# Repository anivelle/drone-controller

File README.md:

# PID Drone Controller

This is my repository for the drone controller I am building using the Arduino
Nano 33 BLE. This is an exercise for me in working directly with the Arduino's
hardware peripherals, as well as learning about PID (I have never taken a
feedback control course).

I'll be using some sort of time of flight (TOF) sensor to give the drone the
ability to hover at a certain height, along with a 9-axis IMU (currently the
BNO055 because I have it) to keep the drone stabilized in the air. That is all
that is currently planned, but if I enjoy this enough I might try autonomous
movement.

ICM-20948 code pulled from [Sparkfun's Arduino
Library](https://github.com/sparkfun/SparkFun_ICM-20948_ArduinoLibrary/tree/main)
because it turns out the DMP-related code is far more complex than I need to
work with. I am trying to reinvent the wheel, but not that much.

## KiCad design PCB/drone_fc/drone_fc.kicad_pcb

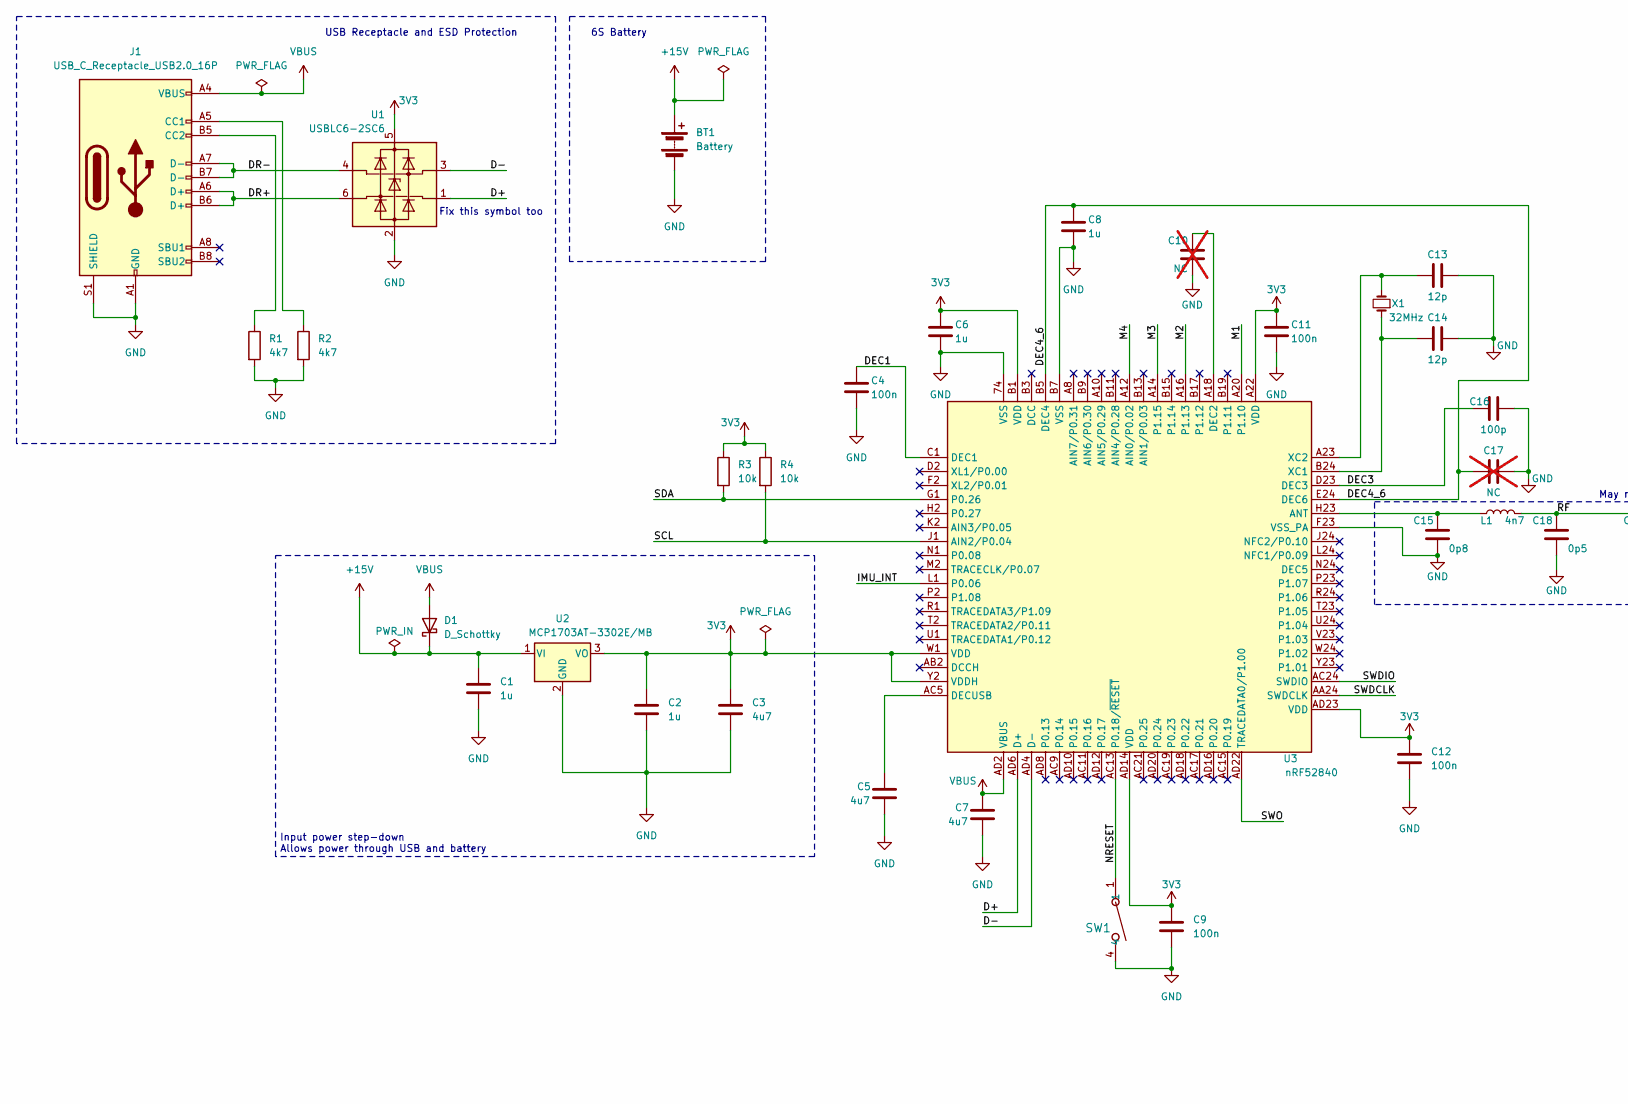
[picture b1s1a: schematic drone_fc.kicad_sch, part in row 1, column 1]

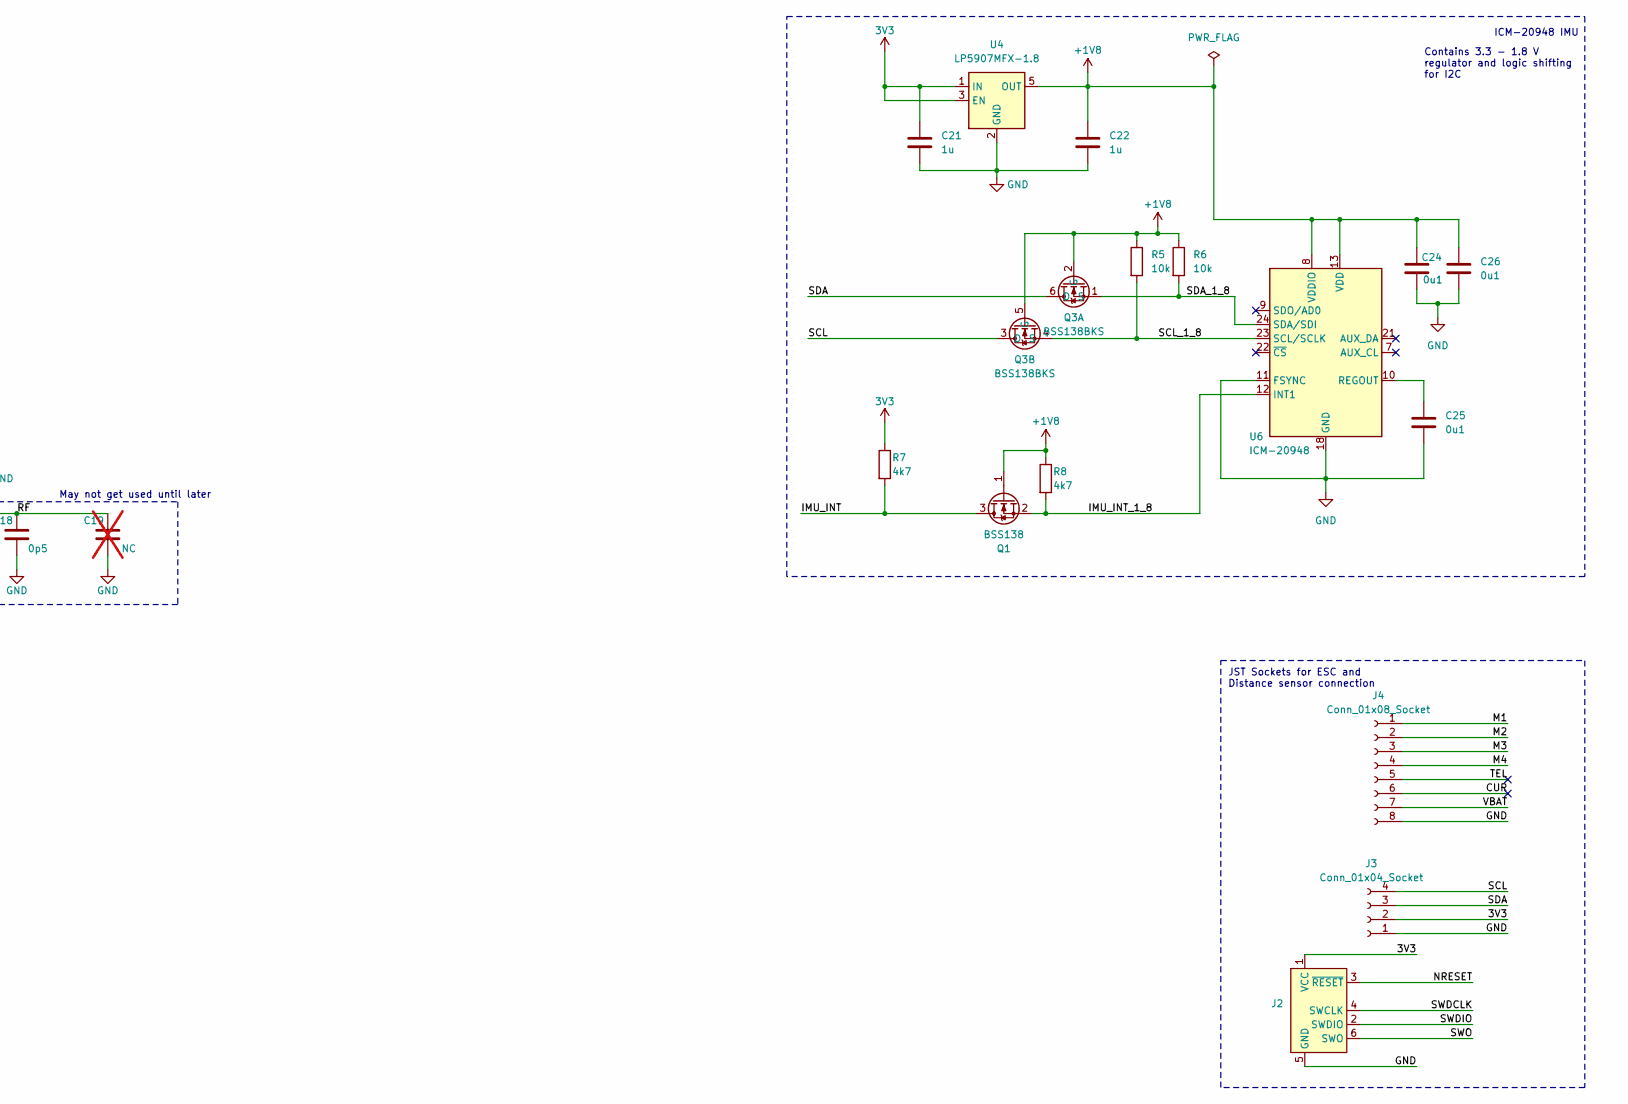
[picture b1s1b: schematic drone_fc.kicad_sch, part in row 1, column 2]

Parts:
BT1: Battery; Pad
C1, C2, C6, C8, C21, C22: 1u; C_0603_1608Metric
C3, C5, C7: 4u7; C_0603_1608Metric
C4, C9, C11, C12: 100n; C_0402_1005Metric
C10, C17, C19: NC; C_0402_1005Metric; not fitted
C13, C14: 12p; C_0402_1005Metric
C15: 0p8; C_0402_1005Metric
C16: 100p; C_0402_1005Metric
C18: 0p5; C_0402_1005Metric
C24, C25, C26: 0u1; C_0402_1005Metric
D1: D_Schottky; Nexperia_CFP3_SOD-123W
J1: USB_C_Receptacle_USB2.0_16P; USB_C_Receptacle_GCT_USB4105-xx-A_16P_TopMnt_Horizontal
J2: Conn_ARM_SWD_TagConnect_TC2030; Tag-Connect_TC2030-IDC-NL_2x03_P1.27mm_Vertical
J3: Conn_01x04_Socket; JST_SH_SM04B-SRSS-TB_1x04-1MP_P1.00mm_Horizontal
J4: Conn_01x08_Socket; JST_SH_SM08B-SRSS-TB_1x08-1MP_P1.00mm_Horizontal
L1: 4n7; L_0402_1005Metric
Q1: BSS138; SOT-323_SC-70
Q3: BSS138BKS; SOT-363_SC-70-6
R1, R2: 4k7; R_0603_1608Metric
R3, R4: 10k; R_0603_1608Metric
R5, R6: 10k; R_0402_1005Metric
R7, R8: 4k7; R_0402_1005Metric
SW1: PTS815SJM250SMTRLFS
U1: USBLC6-2SC6; SOT-23-6
U2: MCP1703AT-3302E/MB; SOT-89-3
U3: nRF52840; Nordic_AQFN-73-1EP_7x7mm_P0.5mm
U4: LP5907MFX-1.8; SOT-23-5
U6: ICM-20948; InvenSense_QFN-24_3x3mm_P0.4mm
X1: 32MHz; Crystal_SMD_2016-4Pin_2.0x1.6mm

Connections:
3V3: C2.1, C3.1, C6.1, C9.1, C11.1, C12.1, C21.1, J2.1 (VCC), J3.2, R3.1, R4.1, R7.1, U1.5 (VBUS), U2.3 (VO), U3.A22 (VDD), U3.AD14 (VDD), U3.AD23 (VDD), U3.B1 (VDD), U3.W1 (VDD), U3.Y2 (VDDH), U4.1 (IN), U4.3 (EN)
+1V8: C22.1, C24.1, C26.1, Q1.1 (G), Q3.2 (G), Q3.5 (G), R5.1, R6.1, R8.1, U4.5 (OUT), U6.8 (VDDIO), U6.13 (VDD)
+15V: BT1.1 (+), C1.1, D1.1 (K), U2.1 (VI)
/CUR: J4.6
/D+: U1.1 (I/O1), U3.AD6 (D+)
/D-: U1.3 (I/O2), U3.AD4 (D-)
/DEC1: C4.1, U3.C1 (DEC1)
/DEC3: C16.1, U3.D23 (DEC3)
/DEC4_6: C8.1, C17.1, U3.B5 (DEC4), U3.E24 (DEC6)
/DR+: J1.A6 (D+), J1.B6 (D+), U1.6 (I/O1)
/DR-: J1.A7 (D-), J1.B7 (D-), U1.4 (I/O2)
/IMU_INT: Q1.3 (D), R7.2, U3.L1 (P0.06)
/IMU_INT_1_8: Q1.2 (S), R8.2, U6.12 (INT1)
/M1: J4.1, U3.A20 (P1.10)
/M2: J4.2, U3.A16 (P1.13)
/M3: J4.3, U3.A14 (P1.15)
/M4: J4.4, U3.A12 (AIN0/P0.02)
/NRESET: J2.3 (~RESET), SW1.1, U3.AC13 (P0.18/~RESET)
/RF: C18.2, C19.2, L1.2
/SCL: J3.4, Q3.3 (D), R4.2, U3.J1 (AIN2/P0.04)
/SCL_1_8: Q3.4 (S), R5.2, U6.23 (SCL/SCLK)
/SDA: J3.3, Q3.6 (D), R3.2, U3.G1 (P0.26)
/SDA_1_8: Q3.1 (S), R6.2, U6.24 (SDA/SDI)
/SWDCLK: J2.4 (SWCLK), U3.AA24 (SWDCLK)
/SWDIO: J2.2 (SWDIO), U3.AC24 (SWDIO)
/SWO: J2.6 (SWO), U3.AD22 (TRACEDATA0/P1.00)
/TEL: J4.5
/VBAT: J4.7
GND: BT1.2 (-), C1.2, C2.2, C3.2, C4.2, C5.2, C6.2, C7.2, C8.2, C9.2, C10.2, C11.2, C12.2, C13.2, C14.2, C15.1, C16.2, C17.2, C18.1, C19.1, C21.2, C22.2, C24.2, C25.2, C26.2, J1.A1 (GND), J1.A12 (GND), J1.B1 (GND), J1.B12 (GND), J1.S1 (SHIELD), J2.5 (GND), J3.1, J4.8, R1.2, R2.2, SW1.4, U1.2 (GND), U2.2 (GND), U3.74 (VSS), U3.B7 (VSS), U3.F23 (VSS_PA), U4.2 (GND), U6.11 (FSYNC), U6.18 (GND), U6.20 (GND)
unnamed: J1.A5 (CC1), R2.1
unnamed: J1.B5 (CC2), R1.1
unnamed: C15.2, L1.1, U3.H23 (ANT)
unnamed: C10.1, U3.A18 (DEC2)
unnamed: C5.1, U3.AC5 (DECUSB)
unnamed: C14.1, U3.B24 (XC1), X1.1
unnamed: C13.1, U3.A23 (XC2), X1.3
unnamed: C25.1, U6.10 (REGOUT)
VBUS: C7.1, D1.2 (A), J1.A4 (VBUS), J1.A9 (VBUS), J1.B4 (VBUS), J1.B9 (VBUS), U3.AD2 (VBUS)

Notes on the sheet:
6S Battery
JST Sockets for ESC and Distance sensor connection
Contains 3.3 - 1.8 V regulator and logic shifting for I2C
ICM-20948 IMU
USB Receptacle and ESD Protection
Input power step-down Allows power through USB and battery
May not get used until later
Fix this symbol too

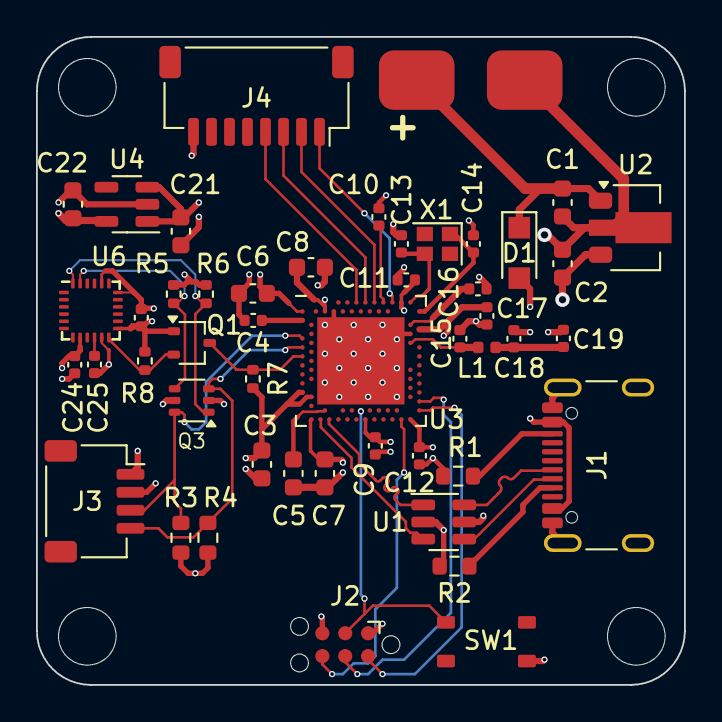
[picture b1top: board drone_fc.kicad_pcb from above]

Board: 4 copper layers, 36.0 x 36.0 mm, 48 parts (0 on the bottom side), 35 nets.

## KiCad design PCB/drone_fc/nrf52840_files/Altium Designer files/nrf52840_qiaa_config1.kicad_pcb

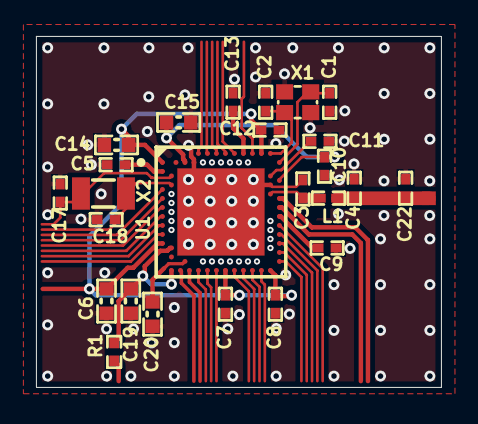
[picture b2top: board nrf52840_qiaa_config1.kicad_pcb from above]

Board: 4 copper layers, 22.5 x 19.5 mm, 25 parts (0 on the bottom side), 15 nets.

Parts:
C1, C2: 12pF; CAPC1005X04L
C3: 0.8pF; CAPC1005X04L
C4: 0.5pF; _Applications_test_rsk_lib_RSK-ONLY_PcbLib_Passive.PcbLib_C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
C5, C7, C8: 100nF; CAPC1005X04L
C6, C19, C20: 4.7µF; _Applications_test_rsk_lib_RSK-ONLY_PcbLib_Passive.PcbLib_C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
C9: 820pF; CAPC1005X04L
C10, C13: N.C.; _Applications_test_rsk_lib_RSK-ONLY_PcbLib_Passive.PcbLib_C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
C11: 100pF; _Applications_test_rsk_lib_RSK-ONLY_PcbLib_Passive.PcbLib_C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
C12: 100nF; _Applications_test_rsk_lib_RSK-ONLY_PcbLib_Passive.PcbLib_C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
C14, C15: 1.0µF; _Applications_test_rsk_lib_RSK-ONLY_PcbLib_Passive.PcbLib_C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
C17, C18: 12pF; _Applications_test_rsk_lib_RSK-ONLY_PcbLib_Passive.PcbLib_C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
C22: N.C.; _Application_test_rsk_lib_RSK-ONLY_PcbLib_Passive.PcbLib_CA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
L1: 4.7nH; INDC1005X04L
R1: 2R2; _Applications_test_rsk_lib_RSK-ONLY_PcbLib_Passive.PcbLib_R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
U1: nRF52840-QIAA; _Applications_test_rsk_lib_RSK-ONLY_PcbLib_AQFN50P700X700X8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
X1: 32MHz; BT-XTAL_2016
X2: 32.768kHz; _Repositories_Applications_test_rsk_lib_RSK-ONLY_PcbLib_pcb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

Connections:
DEC1: C5.1, U1.C1
DEC3: C11.1, U1.D23
DEC4_6: C10.2, C15.2, U1.B5, U1.E24
GND: C1.2, C2.2, C3.1, C4.1, C5.2, C6.2, C7.2, C8.2, C9.2, C10.1, C11.2, C12.2, C13.2, C14.2, C15.1, C17.2, C18.2, C19.2, C20.2, C22.2, U1.74, U1.B7, U1.F23, X1.2, X1.4
NetC3_2: C3.2, L1.1, U1.H23
NetC9_1: C9.1, U1.N24
NetC13_1: C13.1, U1.A18
NetC20_1: C20.1, U1.AC5
P0.00/XL1: C17.1, U1.D2, X2.1
P0.01/XL2: C18.1, U1.F2, X2.2
RF: C4.2, C22.1, L1.2
VBUS_nRF: C19.1, R1.2, U1.AD2, U1.Y2
VDD_NRF: C6.1, C7.1, C8.1, C12.1, C14.1, U1.A22, U1.AD14, U1.AD23, U1.B1, U1.W1
XC1: C1.1, U1.B24, X1.1
XC2: C2.1, U1.A23, X1.3

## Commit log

2023-05-26 Finally found the timer register macros after 3 hours. Off to a great start
2023-05-27 This might work, but I'll need to test tomorrow on the oscilloscope. Removed build files cause they're not necessary for git
2023-05-27 I think I'm getting somewhere. Not all values in the sequence get sent, it seems, but it's better than it was
2023-05-28 It works! Just had to change the compare mode to falling edge
2023-05-29 DShot1200 generation is complete, just need to turn this into a callable function
2023-06-12 Realized I can just use one PWM module, but I do have to interweave the compare values into one sequence to be loaded from RAM, it's a little gross
2023-06-12 I mean it works but the checksum is a little off
2023-06-12 Fixed pinouts
2023-06-21 Okay now the sequence is in order and I know it is correct, need to check PWM output on an oscilloscope
2023-06-28 Made a 'simulation' of the drone in Unity. It's pretty bad but it does give me a visual representation of PID, which I appreciate. I think I may be calculating some of the terms wrong, as it doesn't 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
2023-07-08 This sensor is annoying :)
2023-07-09 Moved PWM and DShot stuff to separate header and source files for organization. Had the distance sensor working, but it seems enabling PWM on this board disables the loop. I thought maybe it was CPU 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
2023-07-09 Small line in pid-drone.ino and removed cache files from Git
2023-07-09 Note: XSHUT has to be connected to pin A1 (or another defined pin) when the sensor is turned on for it to not break everything
2023-07-11 Starting to build up I2C library to use within this project. Looks like the Nano 33 BLE's processor has an easy to use I2C/TWI peripheral so hopefully its a matter of reimplementing the functions in 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
2023-07-14 Well I have no idea if this I2C code works but I'd like to at least find out if the interrupt works. Can't make a volatile variable static to access it without a class object, though, and the compile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
2023-07-31 Moved around the libraries, decided I'm no longer making my own library for I2C, simply because the distance sensor (curse be upon it) is too dependent on Wire.h and I really don't feel like making t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
2023-08-05 I feel like I just redid a bunch of work
2023-08-05 Not even the beeps work, so either DShot is being generated wrong (odd, I had it working previously), or I am completely off base about something
2023-08-18 Well I forgot that the nRF52840 repeats its last duty cycle, so I thought maybe that would fix my motor issues, but no
2023-08-26 Temp commit to switch
2023-08-26 Beginnings of a gyro interface
2023-08-27 More gyroscope library
2023-09-04 The BNO055 library should be right, but nothing works!!! I realized I was using the wrong pins on the Arduino, but that didn't fix it
2023-09-04 I had the address shifted and the pins wrong, and I forgot to try the address unshifted with the pins right. Writes but doesn't read now
2023-09-04 I was using the register address as the requestFrom() address, rather than the BNO055's address. I fixed that error in the data retrieval functions but apparently forgot it in the readRegister() func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
2023-09-05 It works! Updated function definitions to return int16_t, when I returned int the sign didn't read properly. Think I should probably also just update the readRegister() function to accept a length, t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
2023-09-09 Added a small state machine, set up a calibration state and have the IMU printing absolute orientation. No hardware interrupt from the IMU, so I'm setting up a small timer interrupt on the Arduino. N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
2023-09-09 No idea why the interrupt won't work. Compare events also seem to happen irregularly, so I can't trust them. I can use the standard millis() and prevTime method I'm using now, but I don't like it
2023-09-09 Well I've got it working with mbed API calls, but I don't like this method. I may take a look at the underlying code to see where I'm going wrong
2023-09-09 Changed data reading frequency but also I forgot I had library changes to add
2023-09-10 Well I tried some more interrupt register stuff, and I think this is the best I'm getting. Still no clue why it doesn't work for me. May have to try on a clean project
2023-09-16 Fixed DShot but the ESC has pull-ups on the motor wires and also the Arduino does not respond to resets
2023-10-16 Changed: Moved the VL53L4CX header bundle into a library so I could use it in all the sketches without having to copy it over and over. Also this could have been on a different branch but I did add t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
2023-12-16 Just trying out the hardware timer again, forgot to commit this ages ago
2023-12-18 Okay actually I'm reverting my code for now bringing the new changes in was a bad idea
2024-01-04 I rented an oscilloscope to find out I just needed to change the PWM output pin. This works. Now to test the output from the library
2024-01-04 I guess I forgot to add the commented code and the library I merged
2024-01-07 Starting a PCB to replace a whole Nano, man is the chip complicated
2024-01-13 Starting a PCB with the nRF52840. The Nordic-provided boards crash KiCAD so I'm making it myself I guess
2024-01-13 Reusing symbols and footprints from the Phil's Lab video on an STM32-based board
2024-01-13 Of course Git doesn't follow a symbolic link
2024-01-13 Finished basic configuration schematic for nRF52840 and added USB receptacle and ESD protection
2024-01-14 Added voltage regulator after hours of thinking about it too hard
2024-01-14 Going to ignore KiCAD backups for now
2024-01-14 Well the BNO055 isn't recommended for new projects, so I've replaced it with the ICM-20948, and updated the PCB's edge to hopefully match the ESC
2024-01-15 Routed out the nRF52840 so I could tell which pins were best for peripherals
2024-01-16 DShot/PWM libraries have been fixed to actually work with every motor now
2024-01-16 Whoops, forgot to actually add the libraries, needs a new PR I guess
2024-01-16 Trying to reverse motor direction has me going crazy
2024-01-24 The BNO055 is marked as not recommended for new designs so I think I'll move the final design to the ICM-20948, which does mean I need a new library
2024-01-25 Adjusted PCB size to more accurately match the ESC and added MOSFETs to provide logic level shifting on the I2C lines between the uC and IMU (thanks Adafruit and Digikey)
2024-02-06 Many new additions but importantly new MOSFETs for logic shifting (2 in 1 chip), some models to go with footprints on the JST connectors, and a footprint for battery power. Why did I choose such a sm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
2024-02-21 Trying out both Zephyr and Mbed OS, currently looking like I may be able to use Zephyr with a user library to integrate the necessary Arduino functions (mostly Wire.h). I don't particularly want to u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
2024-02-22 Brought in distance sensor code to test if Zephyr is actually capable of using it with the Arduino Core repository but haven't tested it yet. Luckily Zephyr also includes the nRF52840 register mappin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
2024-03-03 Configuration changes and an extra board overlay (both adapted from the Zephyr documentation) were necessary for serial communication to work. Distance sensor is spitting out garbage values though, w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
2024-03-08 Removed mbed-related code
2024-03-11 Wrote wrapper functions and some register definitions for easier access to the ICM20948 gyroscope. Considering switching my distance sensor to the VL53L1X because Zephyr has actual drivers for it. Ma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
2024-04-14 Finally got around to setting up a thread and interrupt to try and read the ICM20948 FIFO. Something's wrong, not sure what though. Perhaps the thread isn't getting called.
2024-04-14 Yeah something's just wrong with the interrupt, will find out later
2024-12-07 New parts and footprints for existing resistors. Still some work to be done on checking battery voltage and PCB layout
2024-12-20 Still figuring out interrupts. Tried using GPIO driver to implement it but somewhere along the way I have broken the UART functionality and now I cannot get serial output. I do not know if the GPIO m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
2024-12-20 Might have been caused by removing the app.overlay file from CMake but this still isn't working
2024-12-20 Back to the start, I think maybe some other configuration needs to be done on the pins? Really don't know what's not working here
2025-02-23 Using the threads seems to block console output. Currently just running in a loop and polling, discovered that the ICM20948 turns on in sleep mode, and it is obviously unusable like this. Also looks 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
2025-02-23 Working with the ICM20948 is more work than I anticipated. While rewriting the DMP code myself could be nice, I'm more interested in just getting it working (and I suspect I'll already have my work c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
2025-04-15 Modified Sparkfun library code a bit, and it seems I can 'enable' DMP but looking at the C++ examples there is a whole startup procedure I must do. Next priority I guess
2025-04-16 I feel I have implemented the Sparkfun library fully (including DMP initialization), but I cannot seem to get the quaternion output working. Too many electronics? I don't have a longer power cable fo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
2025-04-19 I tested the Sparkfun code, I can confirm the sensor works. No idea what my code is missing right now
2025-04-27 I'm really not sure what's going on. The IMU works for about a second or two before values fall into what appears to be chaos. Is the IMU uncalibrated? The Sparkfun examples work just fine without an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
2025-04-28 Back to the PCB now that I know the IMU works. I think most of the electrical connections are good (I'm still iffy on the nRF52840's VDD/VBUS stuff for hooking up a battery or USB), so I need to find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
2025-04-29 OH MY GOD. The final issue wasn't even in the ICM-20948. I simply wasn't initializing the Arduino's I2C to properly use Fast Mode (400 kHz), and the ICM-20948 needs Fast Mode to work. I blame Zephyr 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
2025-05-03 Changed reset button, still need a header for SWD, and decided to move to a 4-layer board just to add some difficulty
2025-05-06 Stepping back from PCB to ensure the schematic is actually done and to read up on better PCB design. Will likely start from scratch. Did add mounting holes since I completely forgot that earlier
2025-05-06 Copied STM32duino VL53L4CX and modified it to be C code. Not sure it will actually work yet but building works
2025-05-09 Moved the VL53L4CX code into separate files to match the original library. Probably not important but the file loaded slowly and I thought it was causing issues (it was not). Makes CMakeLists.txt a l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
2025-05-09 Had to pass the register buffer pointer itself, not the address to the register buffer pointer, duh. So much fun trying to find that. Why were there no errors?? Initialization passes now but it doesn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
2025-05-13 Tried some things to debug but I have no idea what's going on. I2C message dumping breaks the system, the I2C shell doesn't load, and reading/writing to the sensor works, so I'm not sure what's up. M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
2025-05-13 It works. My fault it didn't, as explained by the comment in VL53L4CX_I2CWrite(). Now that both sensors work, I'll have to try using both at once, and then adding interrupt code
2025-05-15 It's... done? I still have to create and route the VL53L4CX interrupt signal but otherwise I think this just needs some more grounding. I made sure that vias weren't on top of unrelated traces just i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
2025-05-19 Made sure no traces were under vias and turned them into through holes because JLCPCB doesn't support blind vias and it's cheaper like this anyway
